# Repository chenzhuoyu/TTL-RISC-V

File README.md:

# TTL RISC-V

RISC-V processor & peripherals made (almost) entirely with 74-series TTL logic chips.

This repository contains the KiCAD schematics and PCB drawings of the processor, along with the related software source code.

This is designed to be as simple as possible, but it should be a practical processor rather than a pure-educational one.

## Current Design Goals

* Implements the `RV32IMZicsr_Zifencei` instruction set.
* Runs at least `8MHz` clock speed.
* 2-stage pipelines.
* Interrupts.
* Mostly single clock cycle instructions.
* Supports the 6800 bus interface (e.g. R/W and STROBE signals).
* Bus arbitration to support external DMA controllers or co-processors.

## Future Design Goals (maybe)

* Higher clock speed?
* Deeper pipelines?
* Out-of-order?
* Superscalar? It might require too many chips to implement :(

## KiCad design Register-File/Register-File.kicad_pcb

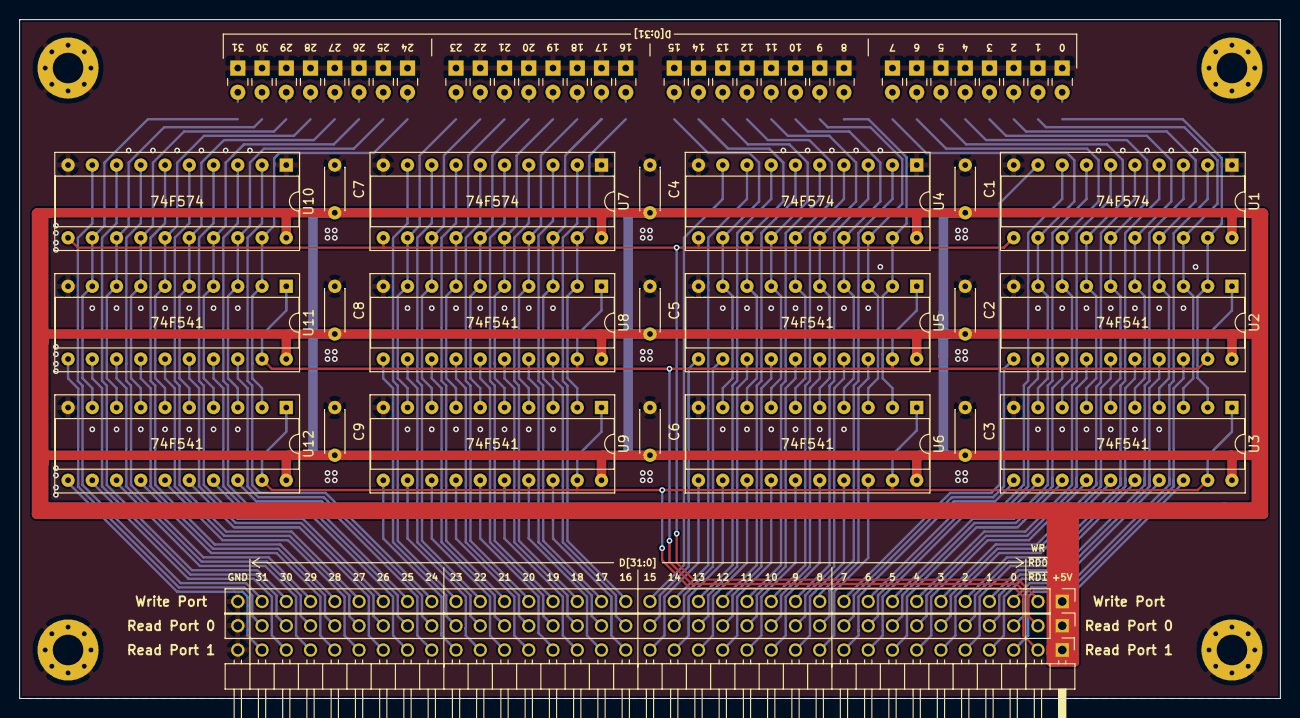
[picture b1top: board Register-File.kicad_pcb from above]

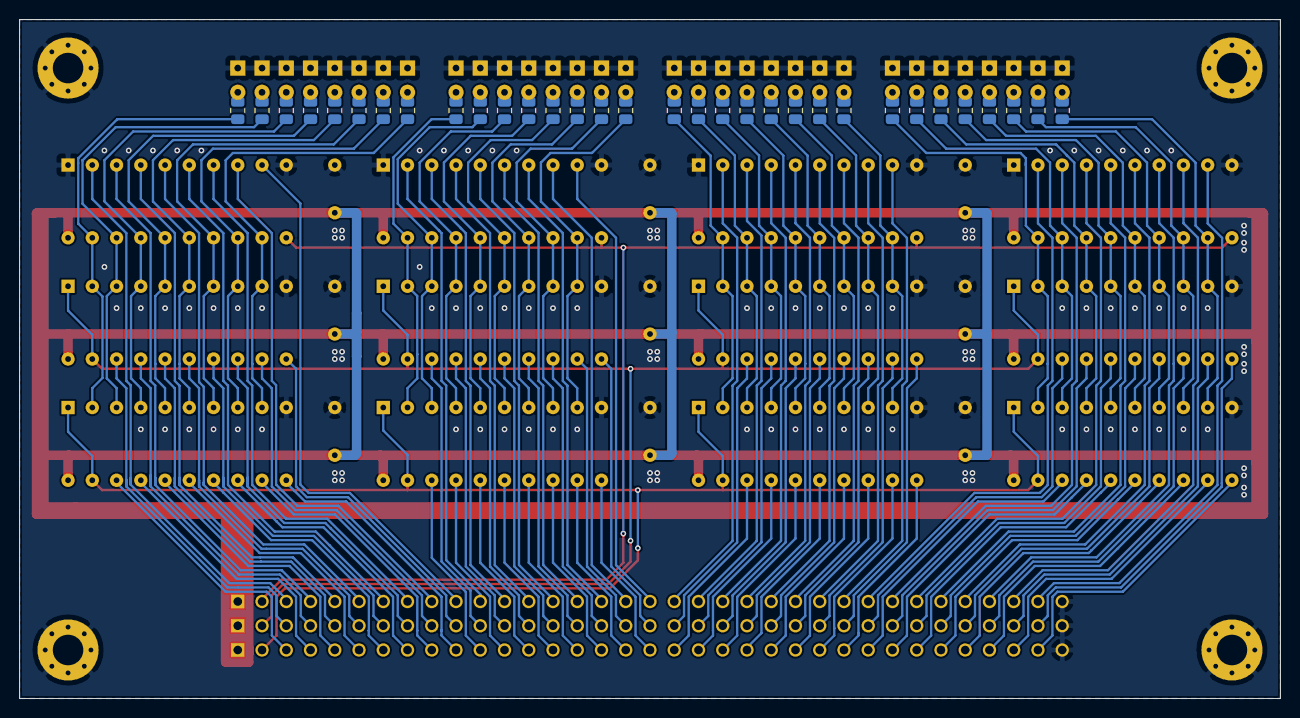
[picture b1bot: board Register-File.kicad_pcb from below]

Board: 2 copper layers, 132.1 x 71.1 mm, 92 parts (32 on the bottom side), 165 nets.

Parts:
C1, C2, C3, C4, C5, C6, C7, C8, C9: C_Small; C_Disc_D4.3mm_W1.9mm_P5.00mm
D1, D2, D3, D4, D5, D6, D7, D8, D9, D10, D11, D12, D13, D14, D15, D16, D17, D18, D19, D20, D21, D22, D23, D24, D25, D26, D27, D28, D29, D30, D31, D32: LED_Small; LED_Rectangular_W3.0mm_H2.0mm
H1, H2, H3, H4: MountingHole_Pad; MountingHole_3.2mm_M3_Pad_Via
J1, J2: Conn_01x35_Male; PinHeader_1x35_P2.54mm_Vertical
J3: Conn_01x35_Male; PinHeader_1x35_P2.54mm_Horizontal
R1, R2, R3, R4, R5, R6, R7, R8, R9, R10, R11, R12, R13, R14, R15, R16, R17, R18, R19, R20, R21, R22, R23, R24, R25, R26, R27, R28, R29, R30, R31, R32: R_Small; R_0805_2012Metric
U1, U4, U7, U10: 74LS574; DIP-20_W7.62mm_Socket
U2, U3, U5, U6, U8, U9, U11, U12: 74LS541; DIP-20_W7.62mm_Socket

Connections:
+5V: C1.1, C2.1, C3.1, C4.1, C5.1, C6.1, C7.1, C8.1, C9.1, J1.1, J2.1, J3.1, U1.20, U2.20, U3.20, U4.20, U5.20, U6.20, U7.20, U8.20, U9.20, U10.20, U11.20, U12.20
/D0: R1.1, U1.19, U2.2, U3.2
/D1: R2.1, U1.18, U2.3, U3.3
/D2: R3.1, U1.17, U2.4, U3.4
/D3: R4.1, U1.16, U2.5, U3.5
/D4: R5.1, U1.15, U2.6, U3.6
/D5: R6.1, U1.14, U2.7, U3.7
/D6: R7.1, U1.13, U2.8, U3.8
/D7: R8.1, U1.12, U2.9, U3.9
/D8: R9.1, U4.19, U5.2, U6.2
/D9: R10.1, U4.18, U5.3, U6.3
/D10: R11.1, U4.17, U5.4, U6.4
/D11: R12.1, U4.16, U5.5, U6.5
/D12: R13.1, U4.15, U5.6, U6.6
/D13: R14.1, U4.14, U5.7, U6.7
/D14: R15.1, U4.13, U5.8, U6.8
/D15: R16.1, U4.12, U5.9, U6.9
/D16: R17.1, U7.19, U8.2, U9.2
/D17: R18.1, U7.18, U8.3, U9.3
/D18: R19.1, U7.17, U8.4, U9.4
/D19: R20.1, U7.16, U8.5, U9.5
/D20: R21.1, U7.15, U8.6, U9.6
/D21: R22.1, U7.14, U8.7, U9.7
/D22: R23.1, U7.13, U8.8, U9.8
/D23: R24.1, U7.12, U8.9, U9.9
/D24: R25.1, U10.19, U11.2, U12.2
/D25: R26.1, U10.18, U11.3, U12.3
/D26: R27.1, U10.17, U11.4, U12.4
/D27: R28.1, U10.16, U11.5, U12.5
/D28: R29.1, U10.15, U11.6, U12.6
/D29: R30.1, U10.14, U11.7, U12.7
/D30: R31.1, U10.13, U11.8, U12.8
/D31: R32.1, U10.12, U11.9, U12.9
/RD0: J2.2, U2.1, U2.19, U5.1, U5.19, U8.1, U8.19, U11.1, U11.19
/RD1: J3.2, U3.1, U3.19, U6.1, U6.19, U9.1, U9.19, U12.1, U12.19
/WD0: J1.3, U1.2
/WD1: J1.4, U1.3
/WD2: J1.5, U1.4
/WD3: J1.6, U1.5
/WD4: J1.7, U1.6
/WD5: J1.8, U1.7
/WD6: J1.9, U1.8
/WD7: J1.10, U1.9
/WD8: J1.11, U4.2
/WD9: J1.12, U4.3
/WD10: J1.13, U4.4
/WD11: J1.14, U4.5
/WD12: J1.15, U4.6
/WD13: J1.16, U4.7
/WD14: J1.17, U4.8
/WD15: J1.18, U4.9
/WD16: J1.19, U7.2
/WD17: J1.20, U7.3
/WD18: J1.21, U7.4
/WD19: J1.22, U7.5
/WD20: J1.23, U7.6
/WD21: J1.24, U7.7
/WD22: J1.25, U7.8
/WD23: J1.26, U7.9
/WD24: J1.27, U10.2
/WD25: J1.28, U10.3
/WD26: J1.29, U10.4
/WD27: J1.30, U10.5
/WD28: J1.31, U10.6
/WD29: J1.32, U10.7
/WD30: J1.33, U10.8
/WD31: J1.34, U10.9
/WR: J1.2, U1.11, U4.11, U7.11, U10.11
/X0: J2.3, U2.18
/X1: J2.4, U2.17
/X2: J2.5, U2.16
/X3: J2.6, U2.15
/X4: J2.7, U2.14
/X5: J2.8, U2.13
/X6: J2.9, U2.12
/X7: J2.10, U2.11
/X8: J2.11, U5.18
/X9: J2.12, U5.17
/X10: J2.13, U5.16
/X11: J2.14, U5.15
/X12: J2.15, U5.14
/X13: J2.16, U5.13
/X14: J2.17, U5.12
/X15: J2.18, U5.11
/X16: J2.19, U8.18
/X17: J2.20, U8.17
/X18: J2.21, U8.16
/X19: J2.22, U8.15
/X20: J2.23, U8.14
/X21: J2.24, U8.13
/X22: J2.25, U8.12
/X23: J2.26, U8.11
/X24: J2.27, U11.18
/X25: J2.28, U11.17
/X26: J2.29, U11.16
/X27: J2.30, U11.15
/X28: J2.31, U11.14
/X29: J2.32, U11.13
/X30: J2.33, U11.12
/X31: J2.34, U11.11
/Y0: J3.3, U3.18
/Y1: J3.4, U3.17
/Y2: J3.5, U3.16
/Y3: J3.6, U3.15
/Y4: J3.7, U3.14
/Y5: J3.8, U3.13
/Y6: J3.9, U3.12
/Y7: J3.10, U3.11
/Y8: J3.11, U6.18
/Y9: J3.12, U6.17
/Y10: J3.13, U6.16
/Y11: J3.14, U6.15
/Y12: J3.15, U6.14
/Y13: J3.16, U6.13
/Y14: J3.17, U6.12
/Y15: J3.18, U6.11
/Y16: J3.19, U9.18
/Y17: J3.20, U9.17
/Y18: J3.21, U9.16
/Y19: J3.22, U9.15
/Y20: J3.23, U9.14
/Y21: J3.24, U9.13
/Y22: J3.25, U9.12
/Y23: J3.26, U9.11
/Y24: J3.27, U12.18
/Y25: J3.28, U12.17
/Y26: J3.29, U12.16
/Y27: J3.30, U12.15
/Y28: J3.31, U12.14
/Y29: J3.32, U12.13
/Y30: J3.33, U12.12
/Y31: J3.34, U12.11
GND: C1.2, C2.2, C3.2, C4.2, C5.2, C6.2, C7.2, C8.2, C9.2, D1.1, D2.1, D3.1, D4.1, D5.1, D6.1, D7.1, D8.1, D9.1, D10.1, D11.1, D12.1, D13.1, D14.1, D15.1, D16.1, D17.1, D18.1, D19.1, D20.1, D21.1, D22.1, D23.1, D24.1, D25.1, D26.1, D27.1, D28.1, D29.1, D30.1, D31.1, D32.1, H1.1, H2.1, H3.1, H4.1, J1.35, J2.35, J3.35, U1.1, U1.10, U2.10, U3.10, U4.1, U4.10, U5.10, U6.10, U7.1, U7.10, U8.10, U9.10, U10.1, U10.10, U11.10, U12.10
unnamed: D1.2, R1.2
unnamed: D2.2, R2.2
unnamed: D3.2, R3.2
unnamed: D4.2, R4.2
unnamed: D5.2, R5.2
unnamed: D6.2, R6.2
unnamed: D7.2, R7.2
unnamed: D8.2, R8.2
unnamed: D9.2, R9.2
unnamed: D10.2, R10.2
unnamed: D11.2, R11.2
unnamed: D12.2, R12.2
unnamed: D13.2, R13.2
unnamed: D14.2, R14.2
unnamed: D15.2, R15.2
unnamed: D16.2, R16.2
unnamed: D17.2, R17.2
unnamed: D18.2, R18.2
unnamed: D19.2, R19.2
unnamed: D20.2, R20.2
unnamed: D21.2, R21.2
unnamed: D22.2, R22.2
unnamed: D23.2, R23.2
unnamed: D24.2, R24.2
unnamed: D25.2, R25.2
unnamed: D26.2, R26.2
unnamed: D27.2, R27.2
unnamed: D28.2, R28.2
unnamed: D29.2, R29.2
unnamed: D30.2, R30.2
unnamed: D31.2, R31.2
unnamed: D32.2, R32.2

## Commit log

2021-09-01 feat: register bank layer 0
2021-09-01 doc: update README
2021-09-01 chore: update README
2021-09-01 feat: add silk screen printing
2021-09-01 fix: fix orientation of the label
2021-09-02 chore: move .gitignore
2021-09-18 feat: redesign the register file
2021-09-19 fix: fix ground filling
2021-09-23 fix: fix LED markings
2021-09-26 fix: enlarge pads for pin header
2021-09-28 feat: immediate decoder circuit & GAL functions
2021-10-14 wip: incomplete simulation
2021-10-15 feat: boolean logic synthesis tool
2021-10-19 feat: it can calculate Fibonacci sequence now
2021-11-02 wip: half-working prototype
2021-11-07 feat: redesign with pipelines
2021-11-12 feat: operand forwarding
2021-11-15 feat: load instructions is now working
2021-11-20 feat: properly timed pipeline (no Load & Store)
2021-11-20 chore: update README.md
2021-11-20 chore: circuit cleanup
2021-11-20 chore: shrink the size of arithmetic decoder
2021-11-26 feat: first working implementation
2021-11-30 feat: CSR decoder
2021-12-03 feat: CSR read and write
2021-12-04 chore: about to construct the interrupt handler
2021-12-07 wip: half-finished interrupt controller
2021-12-18 feat: part of the instruction decoder
2021-12-19 feat: a working design that can run fibonacci
2021-12-28 feat: WFI instruction
2021-12-29 feat: maybe the first complete design
2021-12-30 feat: add test program
2021-12-30 fix: fix ld script
2021-12-30 fix: fix immediate decoding
2022-01-01 feat: display number with ECALL
2022-01-01 chore: save schematics
2022-01-03 fix: fix handling of external interrupts
2022-01-03 chore: simulate at max speed
2022-01-03 feat: optimize interrupt controller
2022-01-03 feat: optimize circuit
2022-01-04 feat: use dedicated CSR Immediate port
2022-01-10 opt: use PLA for interrupt controller
2022-02-09 feat: simplify instruction decoder
2022-02-09 feat: parallel instruction decoder
2022-02-09 fix: fix instruction decoder appearance
2022-02-11 feat: replace decoder ROM with PLA
2022-02-11 chore: merge branch and load-store decoder
2022-02-11 fix: fix unexpected PC increment after RESET
2022-02-11 chore: remove unused parts
2022-07-09 chore: update schematics & things
2022-07-09 feat: working divider circuit
2022-07-10 feat: seemingly correct integer division
2022-07-13 feat: 33-bit dadda tree visualization
2022-07-25 feat: add PinIO tool
